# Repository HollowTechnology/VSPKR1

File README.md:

<center><h1>VSPKR1</h1></center>

[Tinkercad URL (STL)](https://www.tinkercad.com/things/8K3mWJbN8PP-vinyl-speaker-1-case)
### What is it?

The VSPKR1 (Vinyl Speaker 1) is an open source alternative to Alexa, Google Home, or a Homepod, but open source (similar to the Home Assistant Voice Preview edition, but also made for music and not only Assist!)<br><br>
It can / will be able to be used with either cloud AI or local Ollama AI (or alternatives), making it maybe smarter than your existing smart speakers!

### Why did I decide to make this?
There are 2 reasons that I decided to make this; First, I wanted to for HackClub! Second, privacy. I have heard that Google Home speakers can spy on you, and listen in to your conversations. I think that is true 100%, so that's why I made this! To De-Google!

### A quick overview on how to build this;

> [!NOTE]
> I unfortunately got a hairline fracture on my arm while working on this project. <br>
> Sorry if this guide is bad in any way!<br>
> Also, this guide assumes you have either a hot plate or a hot air rework station

Step 1. Getting the parts<br>
All of the parts (except the PCB) are in the BOM.csv file with Digikey Part ID's for each part and quantities.<br>
Order those to get started!<br>
Make sure to also get the case 3D printed from somewhere (PCBWay can make the PCB + 3D Printed case!)
<br><br>
Step 2. Ordering PCB<br>
For this, open the `pcb` folder in the root of this repo as a project in KiCad. Then, you can export the gerber files from the `File` menu.<br>
From there, you can then order that PCB from your preferred PCB manufacturer.
<br><br>
Step 3. Build it!<br>
Once all the parts and PCB have arrived, you can then use a hot plate or hot air rework station, assuming you have one to solder all the parts to the PCB. For easier soldering, take a look at the PCB viewer in KiCad on a monitor while soldering.
<br><br>
Step 4. Flash ESPHome<br>
Follow the guide at `esphome.io` to flash the board with ESPHome firmware
<br><br>
Step 5. VSPKR1 Firmware<br>
Connect the PCB to your computer and drag and drop the `ESPHome.yaml` file from the `firmware` folder to the PCB, when it shows up as a USB Drive. You are done! Enjoy your speaker!

### Screnshots:

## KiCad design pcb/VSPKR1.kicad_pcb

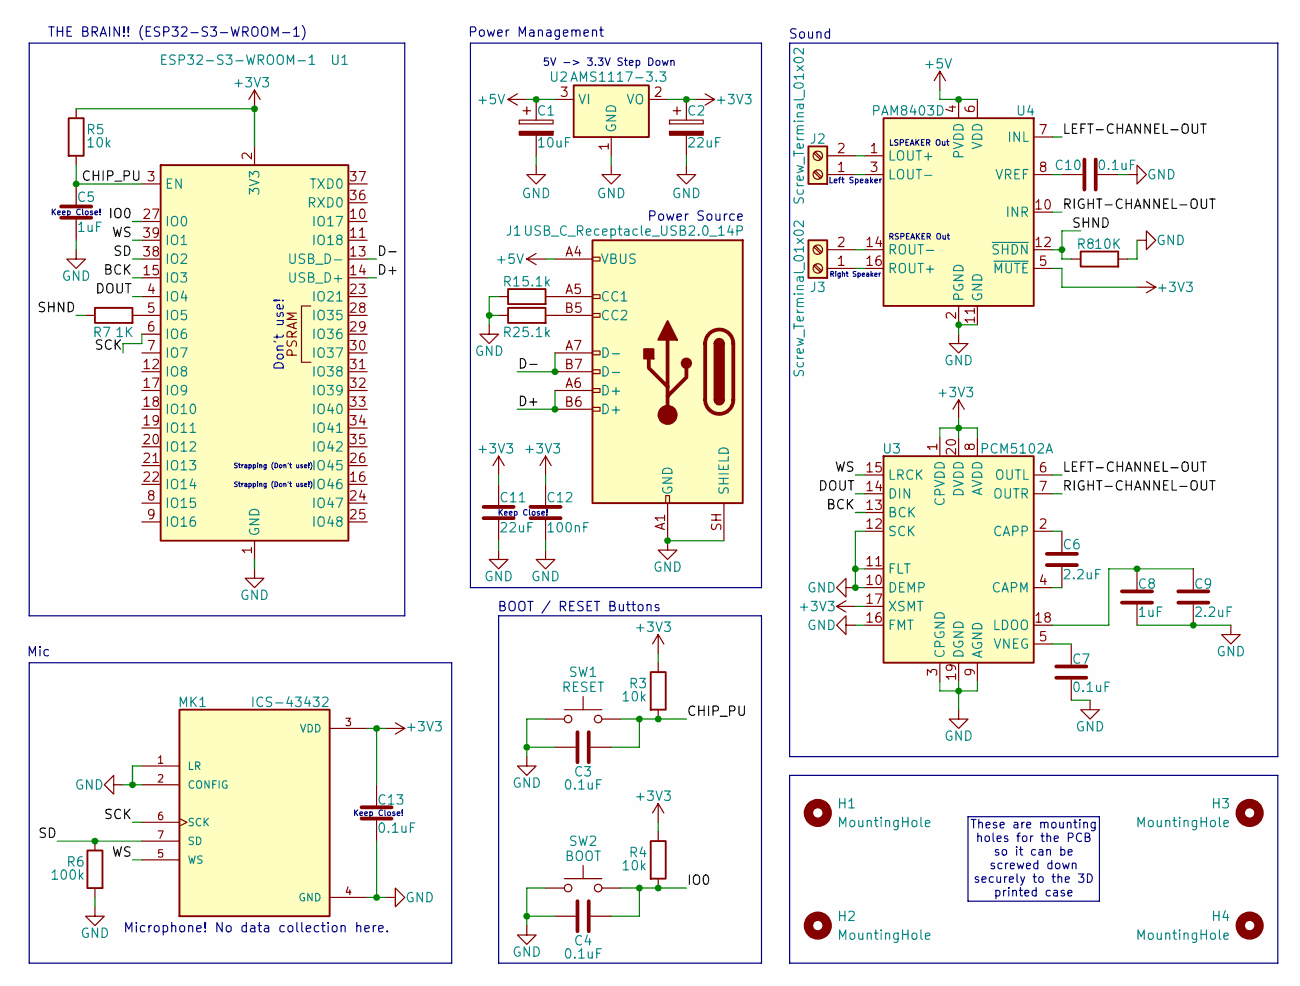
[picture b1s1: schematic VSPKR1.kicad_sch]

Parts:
C1: 10uF; C_0805_2012Metric_Pad1.18x1.45mm_HandSolder
C2, C11: 22uF; C_0805_2012Metric_Pad1.18x1.45mm_HandSolder
C3, C4, C7, C10, C13: 0.1uF; C_0805_2012Metric_Pad1.18x1.45mm_HandSolder
C5, C8: 1uF; C_0805_2012Metric_Pad1.18x1.45mm_HandSolder
C6, C9: 2.2uF; C_0805_2012Metric_Pad1.18x1.45mm_HandSolder
C12: 100nF; C_0805_2012Metric_Pad1.18x1.45mm_HandSolder
H1, H2, H3, H4: MountingHole; MountingHole_2.2mm_M2
J1: USB_C_Receptacle_USB2.0_14P; USB_C_Receptacle_GCT_USB4105-xx-A_16P_TopMnt_Horizontal
J2, J3: Screw_Terminal_01x02; TerminalBlock_Phoenix_MKDS-1,5-2_1x02_P5.00mm_Horizontal
MK1: ICS-43432; MIC_ICS-43432; PARTREV 1.3
R1, R2: 5.1k; R_0805_2012Metric_Pad1.20x1.40mm_HandSolder
R3, R4, R5: 10k; R_0805_2012Metric_Pad1.20x1.40mm_HandSolder
R6: 100k; R_0805_2012Metric_Pad1.20x1.40mm_HandSolder
R7: 1K; R_0805_2012Metric_Pad1.20x1.40mm_HandSolder
R8: 10K; R_0805_2012Metric_Pad1.20x1.40mm_HandSolder
SW1: RESET; SW_Push_1P1T_NO_CK_PTS125Sx43SMTR
SW2: BOOT; SW_Push_1P1T_NO_CK_PTS125Sx43SMTR
U1: ESP32-S3-WROOM-1
U2: AMS1117-3.3; SOT-223-3_TabPin2
U3: PCM5102A; TSSOP-20_4.4x6.5mm_P0.65mm
U4: PAM8403D; SOIC-16_3.9x9.9mm_P1.27mm

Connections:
+3V3: C2.1, C11.1, C12.1, C13.1, MK1.3 (VDD), R3.1, R4.1, R5.1, U1.2 (3V3), U2.2 (VO), U3.1 (CPVDD), U3.8 (AVDD), U3.17 (XSMT), U3.20 (DVDD), U4.5 (~MUTE)
+5V: C1.1, J1.A4 (VBUS), J1.A9 (VBUS), J1.B4 (VBUS), J1.B9 (VBUS), U2.3 (VI), U4.4 (PVDD), U4.6 (VDD), U4.13 (PVDD)
/BCK: U1.15 (IO3), U3.13 (BCK)
/CHIP_PU: C3.2, C5.1, R3.2, R5.2, SW1.2, U1.3 (EN)
/D+: J1.A6 (D+), J1.B6 (D+), U1.14 (USB_D+)
/D-: J1.A7 (D-), J1.B7 (D-), U1.13 (USB_D-)
/DOUT: U1.4 (IO4), U3.14 (DIN)
/IO0: C4.2, R4.2, SW2.2, U1.27 (IO0)
/LEFT-CHANNEL-OUT: U3.6 (OUTL), U4.7 (INL)
/RIGHT-CHANNEL-OUT: U3.7 (OUTR), U4.10 (INR)
/SCK: MK1.6 (SCK), U1.6 (IO6)
/SD: MK1.7 (SD), R6.1, U1.38 (IO2)
/SHND: R7.1, R8.1, U4.12 (~SHDN)
/WS: MK1.5 (WS), U1.39 (IO1), U3.15 (LRCK)
GND: C1.2, C2.2, C3.1, C4.1, C5.2, C7.2, C8.2, C9.2, C10.2, C11.2, C12.2, C13.2, J1.A1 (GND), J1.A12 (GND), J1.B1 (GND), J1.B12 (GND), J1.SH (SHIELD), MK1.1 (LR), MK1.2 (CONFIG), MK1.4 (GND), R1.1, R2.1, R6.2, R8.2, SW1.1, SW2.1, U1.1 (GND), U1.40 (GND), U1.41 (GND), U2.1 (GND), U3.3 (CPGND), U3.9 (AGND), U3.10 (DEMP), U3.11 (FLT), U3.12 (SCK), U3.16 (FMT), U3.19 (DGND), U4.2 (PGND), U4.11 (GND), U4.15 (PGND)
unnamed: J1.A5 (CC1), R1.2
unnamed: J1.B5 (CC2), R2.2
unnamed: J2.1, U4.3 (LOUT-)
unnamed: J2.2, U4.1 (LOUT+)
unnamed: J3.1, U4.16 (ROUT+)
unnamed: J3.2, U4.14 (ROUT-)
unnamed: R7.2, U1.5 (IO5)
unnamed: C6.2, U3.4 (CAPM)
unnamed: C6.1, U3.2 (CAPP)
unnamed: C8.1, C9.1, U3.18 (LDOO)
unnamed: C7.1, U3.5 (VNEG)
unnamed: C10.1, U4.8 (VREF)

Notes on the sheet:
Sound
Strapping (Don't use!)
RSPEAKER Out
Keep Close!
Power Source
BOOT / RESET Buttons
Don't use!
Microphone! No data collection here.
Mic
These are mounting holes for the PCB so it can be screwed down securely to the 3D printed case
5V -> 3.3V Step Down
Right Speaker
Power Management
Left Speaker
LSPEAKER Out
THE BRAIN!! (ESP32-S3-WROOM-1)

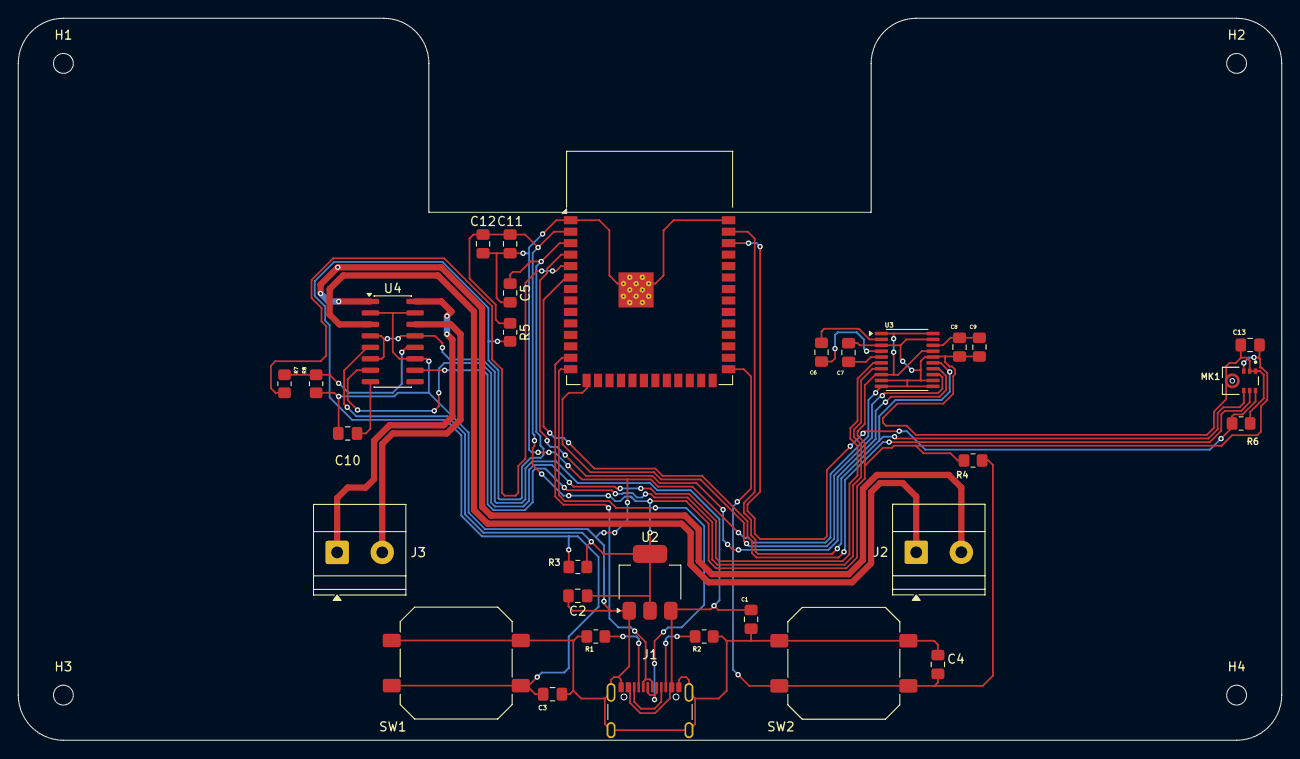
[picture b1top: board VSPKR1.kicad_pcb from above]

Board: 2 copper layers, 140.0 x 80.0 mm, 35 parts (0 on the bottom side), 27 nets.

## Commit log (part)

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2026-04-18 Add PCB stuff
2026-04-18 i made a readme
2026-04-18 added speaker stuffs
    but i havent actually connected it to esp32
2026-04-22 pcb time!!111!!!!1!
2026-05-03 git push -m "hmm"
2026-05-05 Routing PCB traces
2026-05-24 Finished the PCB
2026-06-11 Add image and Tinkercad link to README
    Updated README with image and Tinkercad URL.
2026-06-11 Added Fallout Zine
2026-06-17 Add speaker drivers to BOM.csv
    Added speaker drivers to the BOM with details.
2026-06-17 Create f
2026-06-17 Update README with installation instructions
    Added installation steps and notes for building VSPKR1 speaker.
2026-06-17 Update README with project motivations and build guide
    Added reasons for creating VSPKR1 and installation overview.
2026-06-21 Added STL and STEP and f3d files
2026-06-21 Add README for models directory
2026-06-21 Add screenshots section to README
    Added a section for screenshots to the README.
2026-06-21 Change image in README from GITHUB to Fallout Zine
    Updated image source in README.md to reflect new content.
2026-06-22 Change image source for Fallout Zine
    Updated image source in README from GitHub link to local file.
